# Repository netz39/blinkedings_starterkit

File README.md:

# Starterkit

## v1

Erste Version für den Tag der offenen Tür im März 2013 und für den *AVR 101* Workshop auf der OHM2013.

### Teileliste
* USB-Buchse: USB BW
  * alternative (Stecker): USB AG-KV
* LED (smd): LRTB G6TG
  * alternative: LED RGB5 DIFFUS
* ATTiny: ATiny 85-20 PU
* LM2940 (Spannungsregler): LM 2940 CT5
* Kondensatoren:
  * Ladekondensator(>=22μF, elko): RAD FC 47/25
  * 2 * 100nF: Z5U-2,5 100N
* Platinen: BEL 160X100-1

CC-BY-SA 2.0 24367dfa & bastinat0r @ netz39
-- no military use --

## v2.x
Complete new design started at OHM2013 …

### Part List
* see our [Wiki](http://www.netz39.de/wiki/projects:2013:avr_starterkit#teile1)

### License
mood39 aka Starterkit v2.x von Netz39 e.V. is licensed under the [Creative Commons Attribution-ShareAlike 3.0 Unported License]( http://creativecommons.org/licenses/by-sa/3.0/).

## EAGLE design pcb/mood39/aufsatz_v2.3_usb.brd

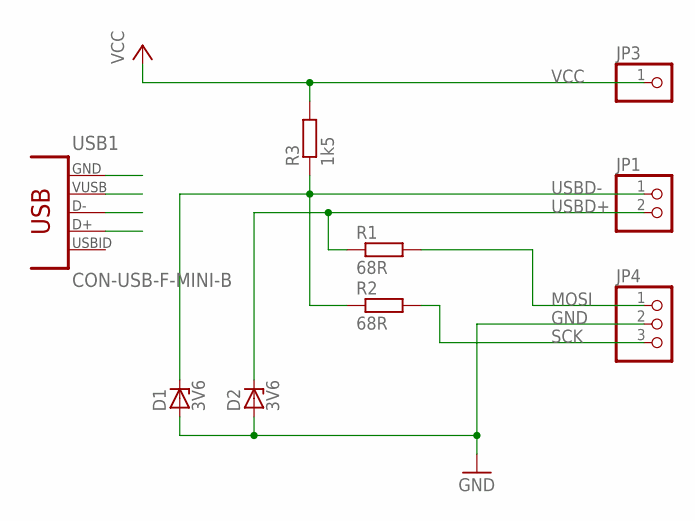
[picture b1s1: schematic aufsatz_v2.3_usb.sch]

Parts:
D1, D2: 3V6; SOD80C
JP1: PINHD-1X2; 1X02
JP3: PINHD-1X1; 1X01
JP4: PINHD-1X3; 1X03
R1, R2: 68R; R0805
R3: 1k5; R0805
USB1: CON-USB-F-MINI-B; CONN_USB_MINI-B

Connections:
GND: D1.A, D2.A, JP4.2, USB1.GND
MOSI: JP4.1, R1.2
SCK: JP4.3, R2.2
USBD+: D2.C, JP1.2, R1.1, USB1.D+
USBD-: D1.C, JP1.1, R2.1, R3.1, USB1.D-
VCC: JP3.1, R3.2, USB1.VUSB

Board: 2 copper layers, 9 parts (0 on the bottom side), 6 nets, no tracks yet.

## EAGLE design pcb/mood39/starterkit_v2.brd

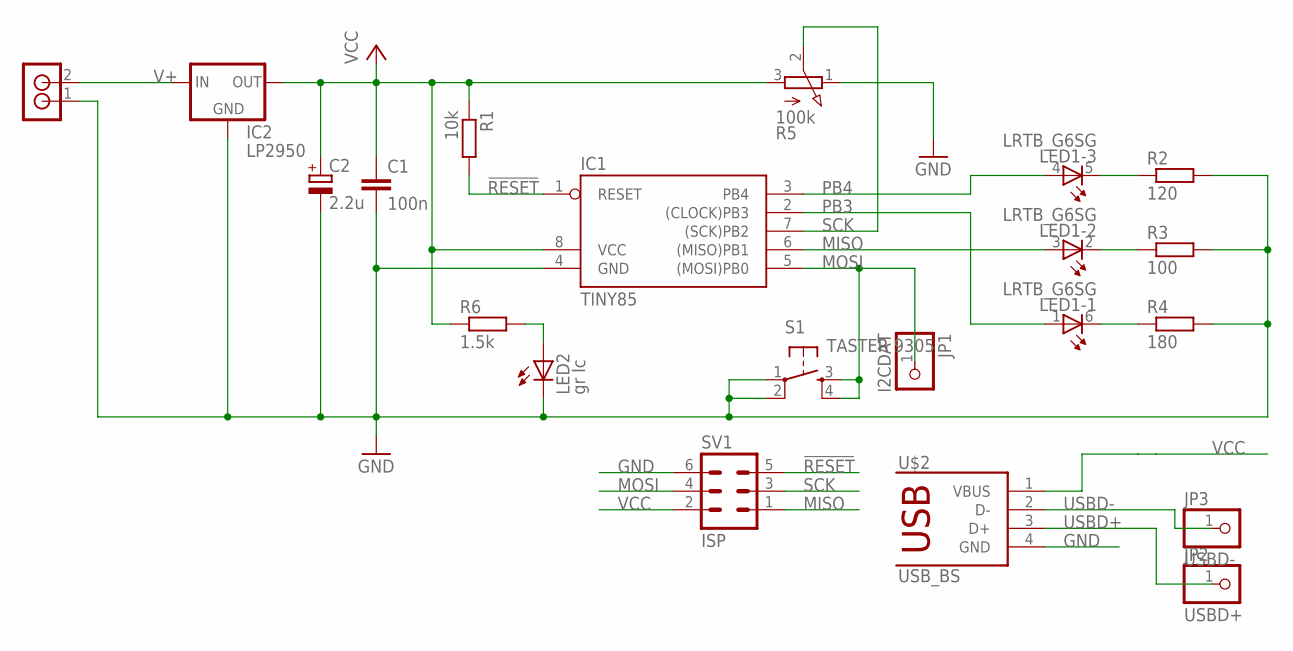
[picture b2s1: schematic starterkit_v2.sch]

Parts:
C1: 100n; C0805
C2: 2.2u; E2-5
IC1: TINY85; DIL08
IC2: LP2950; TO92
JP1: I2CDAT; 1X01
JP2: USBD+; 1X01
JP3: USBD-; 1X01
LED1: LRTB_G6SG
LED2: gr lc; LED3MM
R1: 10k; R0805
R2: 120; R0805
R3: 100; R0805
R4: 180; R0805
R5: 100k; ALPS_RK09K113
R6: 1.5k; R0805
S1: TASTER 9305; JTP-1130
SV1: ISP; ML6
U$1: RIACON_101_2
U$2: USB_BS; USB_B_UP-S

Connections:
!RESET: IC1.1 (RESET), R1.2, SV1.5
GND: C1.2, C2.-, IC1.4 (GND), IC2.2 (GND), LED2.K (C), R2.2, R3.2, R4.2, R5.1 (E), S1.1, S1.2 (P1), SV1.6, U$1.1, U$2.4 (GND)
MISO: IC1.6 ((MISO)PB1), LED1.3 (A), SV1.1
MOSI: IC1.5 ((MOSI)PB0), JP1.1, S1.3 (S), S1.4 (S1), SV1.4
unnamed: LED2.A, R6.2
unnamed: LED1.5 (C), R2.1
unnamed: LED1.2 (C), R3.1
unnamed: LED1.6 (C), R4.1
PB3: IC1.2 ((CLOCK)PB3), LED1.1 (A)
PB4: IC1.3 (PB4), LED1.4 (A)
SCK: IC1.7 ((SCK)PB2), R5.2 (S), SV1.3
USBD+: JP2.1, U$2.3 (D+)
USBD-: JP3.1, U$2.2 (D-)
V+: IC2.3 (IN), U$1.2
VCC: C1.1, C2.+, IC1.8 (VCC), IC2.1 (OUT), R1.1, R5.3 (A), R6.1, SV1.2, U$2.1 (VBUS)

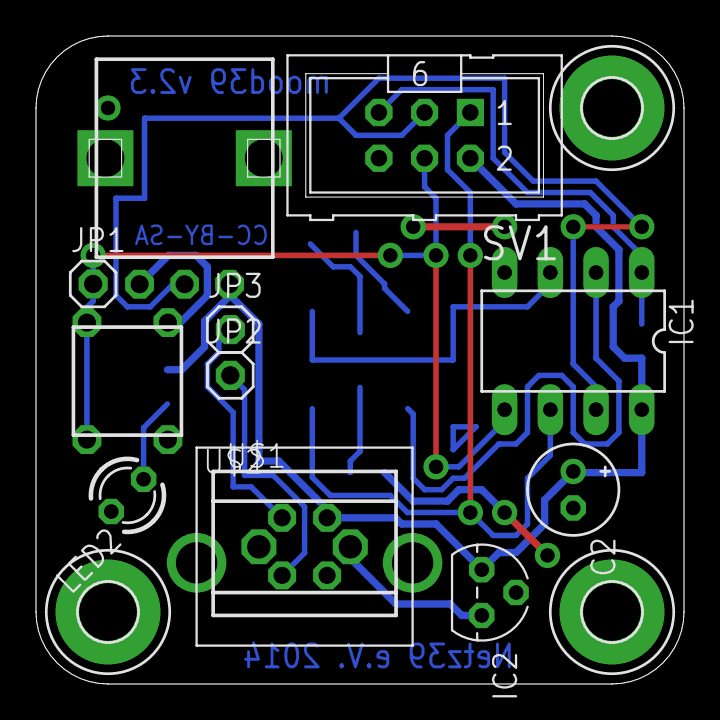
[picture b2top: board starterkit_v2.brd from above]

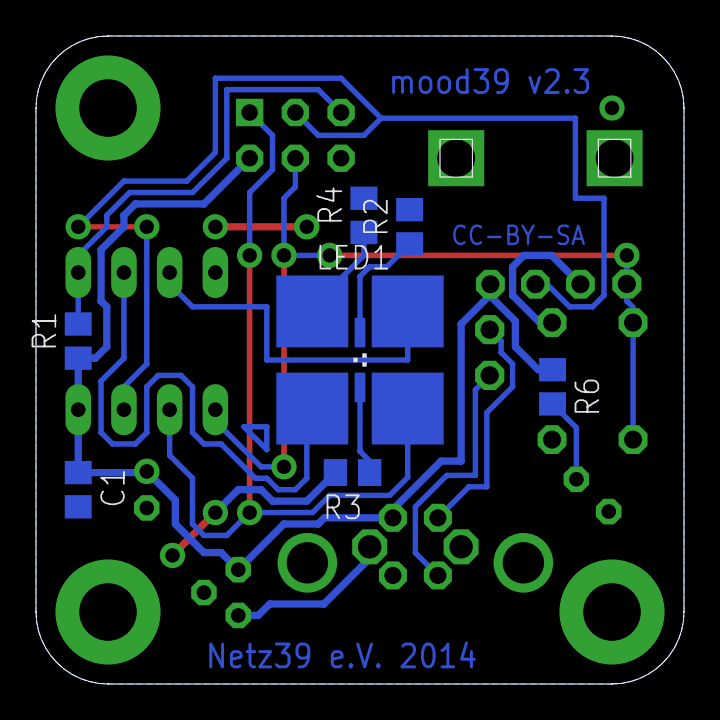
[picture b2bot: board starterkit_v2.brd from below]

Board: 2 copper layers, 36.0 x 36.0 mm, 22 parts (7 on the bottom side), 15 nets.

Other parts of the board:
U$4, U$5, U$6: 3,2-PAD

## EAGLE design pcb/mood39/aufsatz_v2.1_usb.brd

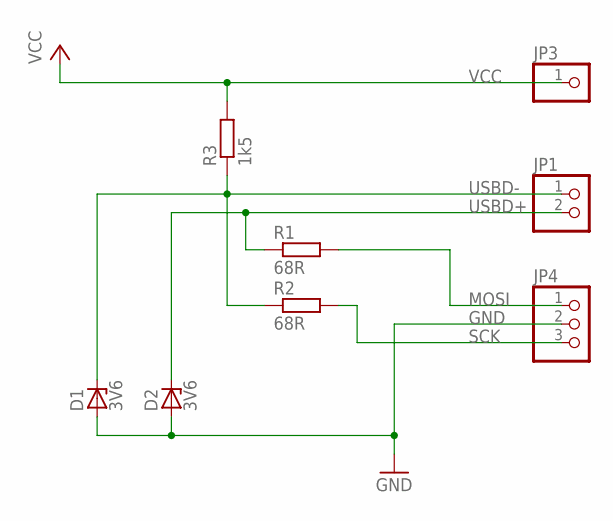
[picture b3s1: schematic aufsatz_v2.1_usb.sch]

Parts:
D1, D2: 3V6; SOD80C
JP1: PINHD-1X2; 1X02
JP3: PINHD-1X1; 1X01
JP4: PINHD-1X3; 1X03
R1, R2: 68R; R0805
R3: 1k5; R0805

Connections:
GND: D1.A, D2.A, JP4.2
MOSI: JP4.1, R1.2
SCK: JP4.3, R2.2
USBD+: D2.C, JP1.2, R1.1
USBD-: D1.C, JP1.1, R2.1, R3.1
VCC: JP3.1, R3.2

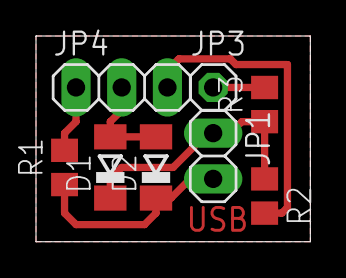
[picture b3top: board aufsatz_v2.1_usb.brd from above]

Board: 2 copper layers, 15.2 x 11.4 mm, 8 parts (0 on the bottom side), 6 nets.

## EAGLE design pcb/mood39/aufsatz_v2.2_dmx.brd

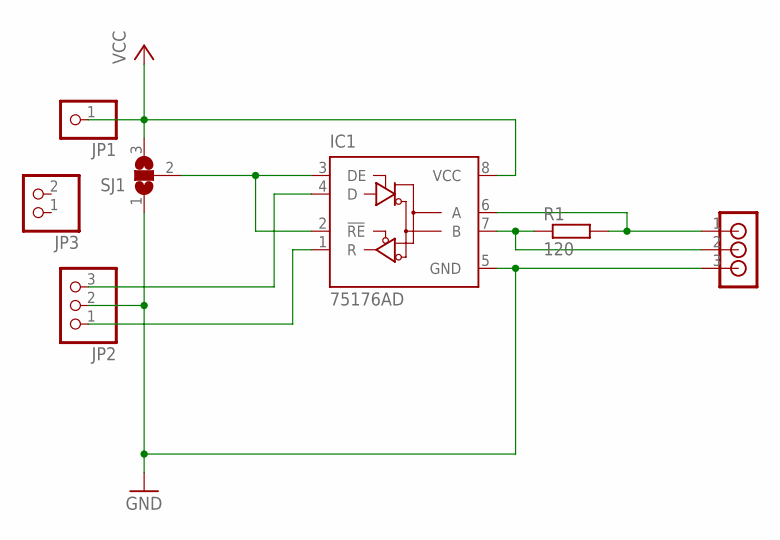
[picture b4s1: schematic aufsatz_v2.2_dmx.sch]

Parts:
IC1: 75176AD; D_R-PDSO-G8
JP1: PINHD-1X1; 1X01
JP2: PINHD-1X3; 1X03
JP3: PINHD-1X2; 1X02
R1: 120; R0805
SJ1: SJ2W; SJ_2
U$1: RIACON_59_3

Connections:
A: IC1.6 (A), R1.2, U$1.1
B: IC1.7 (B), R1.1, U$1.2
D: IC1.4 (D), JP2.3
GND: IC1.5 (GND), JP2.2, SJ1.1, U$1.3
unnamed: IC1.2 (!RE), IC1.3 (DE), SJ1.2
R: IC1.1 (R), JP2.1
VCC: IC1.8 (VCC), JP1.1, SJ1.3

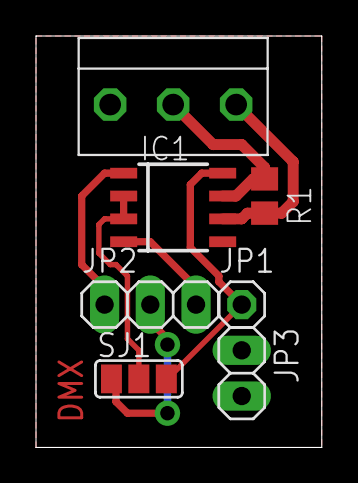
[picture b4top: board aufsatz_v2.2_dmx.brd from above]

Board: 2 copper layers, 15.9 x 22.9 mm, 7 parts (0 on the bottom side), 7 nets.

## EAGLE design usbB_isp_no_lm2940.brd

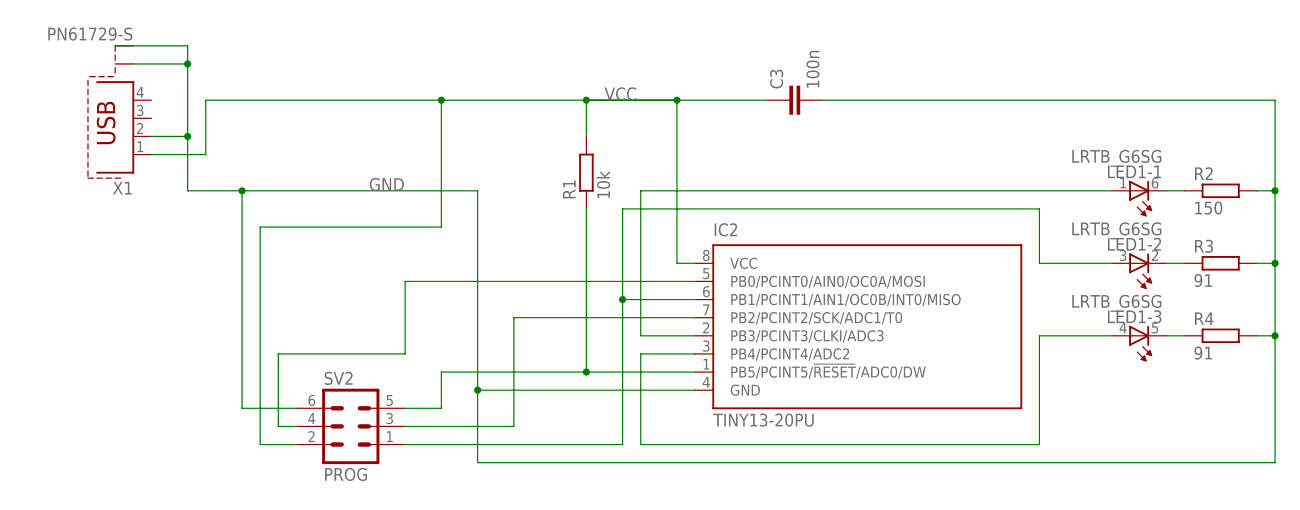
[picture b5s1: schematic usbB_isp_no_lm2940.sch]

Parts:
C3: 100n; C025-025X050
IC2: TINY13-20PU; DIL08
LED1: LRTB_G6SG
R1: 10k; 0207/10
R2: 150; 0207/10
R3, R4: 91; 0207/10
SV2: PROG; ML6
X1: PN61729-S

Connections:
GND: C3.2, IC2.4 (GND), R2.2, R3.2, R4.2, SV2.6, X1.2, X1.S1
MISO: IC2.6 (PB1/PCINT1/AIN1/OC0B/INT0/MISO), LED1.3 (A), SV2.1
unnamed: IC2.2 (PB3/PCINT3/CLKI/ADC3), LED1.1 (A)
unnamed: LED1.5 (C), R4.1
unnamed: LED1.2 (C), R3.1
unnamed: LED1.6 (C), R2.1
unnamed: IC2.3 (PB4/PCINT4/ADC2), LED1.4 (A)
unnamed: IC2.5 (PB0/PCINT0/AIN0/OC0A/MOSI), SV2.4
SCK: IC2.7 (PB2/PCINT2/SCK/ADC1/T0), SV2.3
VCC: C3.1, IC2.8 (VCC), R1.2, SV2.2, X1.1
_RESET: IC2.1 (PB5/PCINT5/!RESET!/ADC0/DW), R1.1, SV2.5

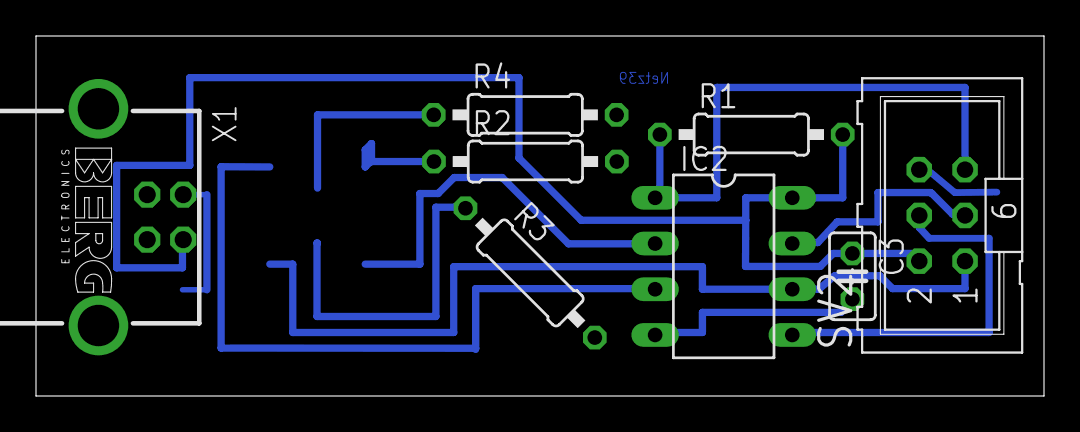
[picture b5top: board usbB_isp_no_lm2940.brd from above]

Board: 2 copper layers, 56.0 x 20.0 mm, 9 parts (1 on the bottom side), 11 nets.

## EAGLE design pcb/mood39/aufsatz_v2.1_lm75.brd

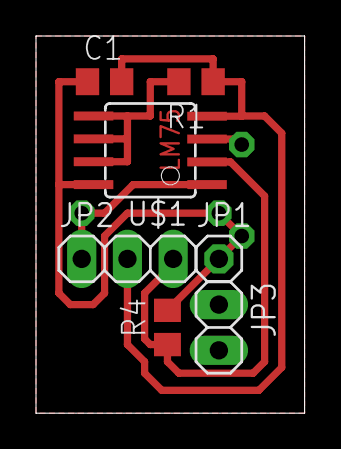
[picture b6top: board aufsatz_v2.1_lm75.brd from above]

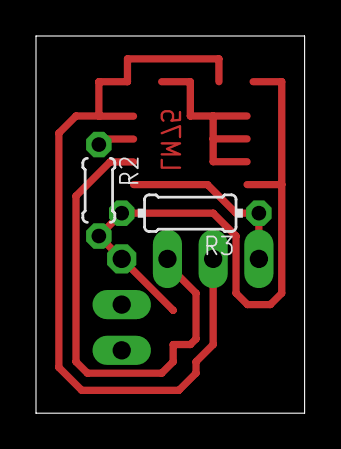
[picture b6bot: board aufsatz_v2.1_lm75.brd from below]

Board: 2 copper layers, 14.9 x 21.0 mm, 9 parts (2 on the bottom side), 6 nets.

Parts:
C1: 100n; C0805
JP1: 1X01
JP2: 1X03
JP3: 1X02
R1: 10k; R0805
R2: 10k; 0204/5
R3: 4k7; 0204/7
R4: 4k7; R0805
U$1: LM75; SOIC8

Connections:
GND: C1.2, JP2.2, R1.1, U$1.4
unnamed: R1.2, U$1.5, U$1.6, U$1.7
unnamed: R2.1, U$1.3
SCL: JP2.3, R4.1, U$1.2
SDA: JP2.1, R3.1, U$1.1
VCC: C1.1, JP1.1, R2.2, R3.2, R4.2, U$1.8

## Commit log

2013-02-19 initial board revision
2013-02-19 Teileliste aktualisiert
2013-02-19 using current cc-license
2013-02-19 minor layout changes
2013-02-20 correct values
2013-02-20 correct pin headers ftw
2013-02-20 Flux Capacitor ... Fluxuated!
2013-02-21 adding sample programm
2013-03-02 isp for b4st1n4t0r
2013-03-02 routing
2013-03-03 fixing some errors i.e. width
2013-03-03 fixed scaling factor
2013-03-03 alignment
2013-03-03 fixing mass pin
2013-03-03 fixing usb-pin GND
2013-03-03 fixing usb-pins
2013-03-03 fixing pdf
2013-03-04 adapted design rules, not DRC done yet
2013-03-04 better GND connection
2013-03-09 done stuff
2013-03-09 adding version without lm2940
2013-03-10 moving some wire
2013-03-10 printing pdf
2013-03-10 waste less space when printing
2013-03-10 wrong pdf-file
2013-03-10 to many layers :
2013-03-10 adjusting writing
2013-03-10 minor adjustments (tm)
2013-03-13 wrong usb-pin *again and again and again and again …
2013-08-03 some structure
2013-08-03 add new eagle project
2013-08-03 basic circuit with uC and LED
2013-08-03 add some connectors and the voltage regulator
2013-08-04 add board (not routed) and design rules
2013-08-04 start routing
2013-08-04 commit before battery low
2013-08-05 routing to a point where the right packages are needed
2013-08-06 der miniaturtaster ist arg groß
2013-08-07 teile ersetzt durch tatsächlich verfügbare
2013-08-07 Taster ersetzt
2013-08-08 add pins for USB data
    those pins can be used for actually accessing the avr via USB, but it
    needs some additional circuit stacked on the pin headers
2013-08-12 replaced USB connector
2013-08-15 proceed routing (this will be fun)
2013-08-16 replace voltage regulator
    this saves one capacitor and lots of space
2013-08-23 proceed routing, still not ready
2013-08-26 routing almost done
2013-08-26 move vias
2013-08-27 routing improved
    after ERC and DRC
2013-08-27 text und marker
2013-08-27 connect GND
    we could give this a try
2013-08-29 letzte Änderungen vor'm Ätzen
2013-08-30 update license in readme
2013-08-30 fix markup
2013-09-04 move uC to top layer
2013-09-06 try another puzzle
2013-09-06 new usb connector package
    this will be puzzling not fun :-/
2013-10-08 proceed routing, hopefully not a dead end
2013-10-08 still two problems, looks like a dead end
2013-10-08 no real improvement, this seemed more promising
2013-10-10 reduced to one problem, looks like a dead end
2013-10-10 connect last signals
    no dead end, phew …
2013-10-10 optimize positions
    (no DRC yet)
2013-10-10 DRC done
2013-10-11 added eagle cam job and svg etch template
2013-10-11 usb aufsatz
2013-10-11 adapt resitor values and add git ignore list
2013-10-11 value for potentiometer
2013-10-11 link to part list and add cam job for add-on board
2013-10-12 add I²C temp sensor extension board
2013-10-13 optimize usb add-on board
2013-10-23 add partlist exported by eagle
2013-10-23 add some documentation
2013-10-23 drahtbrücken noch mit rein
2013-11-08 start optimizing for v2.2
    prevent short circuit
2013-11-16 neues Board, alles bisschen auseinander
2013-11-17 routed
2013-11-17 did DRC
2013-11-17 change text on board
2013-11-18 a little space for a tiny logo
2013-11-18 add little LED orientation hint
2013-11-21 round corners on gnd polygon
2013-12-05 optimize vias
    removed double vias, moved some signals, did DRC again
2013-12-29 cam job for current board revision
2014-01-01 square pad for ISP pin 1 and add documentation
2014-01-01 add CNC reference markers
2014-01-02 target #9
2014-01-02 add DMX addon board
2014-01-02 add descriptive texts
2014-01-10 add old v2.0 from adafruit
2014-01-10 started reworking for single layer board
2014-01-10 update dimensions and change some packages
2014-01-10 unsmash
2014-01-13 vergessene Änderungen
    wenn man nicht alles gleich commited :-/
2014-01-13 move mounting holes inward
2014-01-13 move holes 0.5 mm inward
    this is like dangerousprototypes.com does, I always thought the mounting
    holes were too near to the edges, see
    http://dangerousprototypes.com/docs/Sick_of_Beige_compatible_cases
2014-01-13 replace mounting pads
2014-01-13 swapped some gates and moved all parts around
2014-01-14 routed
    ready for soldering (first test)
2014-01-14 add text, license, and readme
2014-01-14 swap LED1 with resistor
2014-01-15 fix complaints of #11
2014-01-16 moved to https://github.com/netz39/circuit_boards (fixes #13)
2014-01-29 add via for cnc reference and replace mount pads
    Furthermore bump version to v2.3 because we already etched v2.2 and
    changed the board afterwards so e.g. milling some v2.2 is not possible
    with current master anymore. There's still no tag for v2.2 but I guess
    there just won't be any, maybe a branch must be enough for now.
2014-02-16 move assemble sheets to new doc folder
2014-02-16 neues aufsatzboard für USB, nicht fertig
